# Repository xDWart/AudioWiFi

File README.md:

# AudioWiFi
Самодельный USB-свисток с микрофоном, STM32 и ESP8266 на борту

**AudioWiFi.ioc** - проект STM32CubeMX (v.4.15.0)

**EWARM\Project.eww** - проект IAR Embedded Workbench IDE for ARM (v.7.70.1)

**EagleCAD\** - проект EagleCAD (v.7.7.0)

**ogg.php** - файл серверной части на PHP

**20170303172953.spx** - пример записанного звука

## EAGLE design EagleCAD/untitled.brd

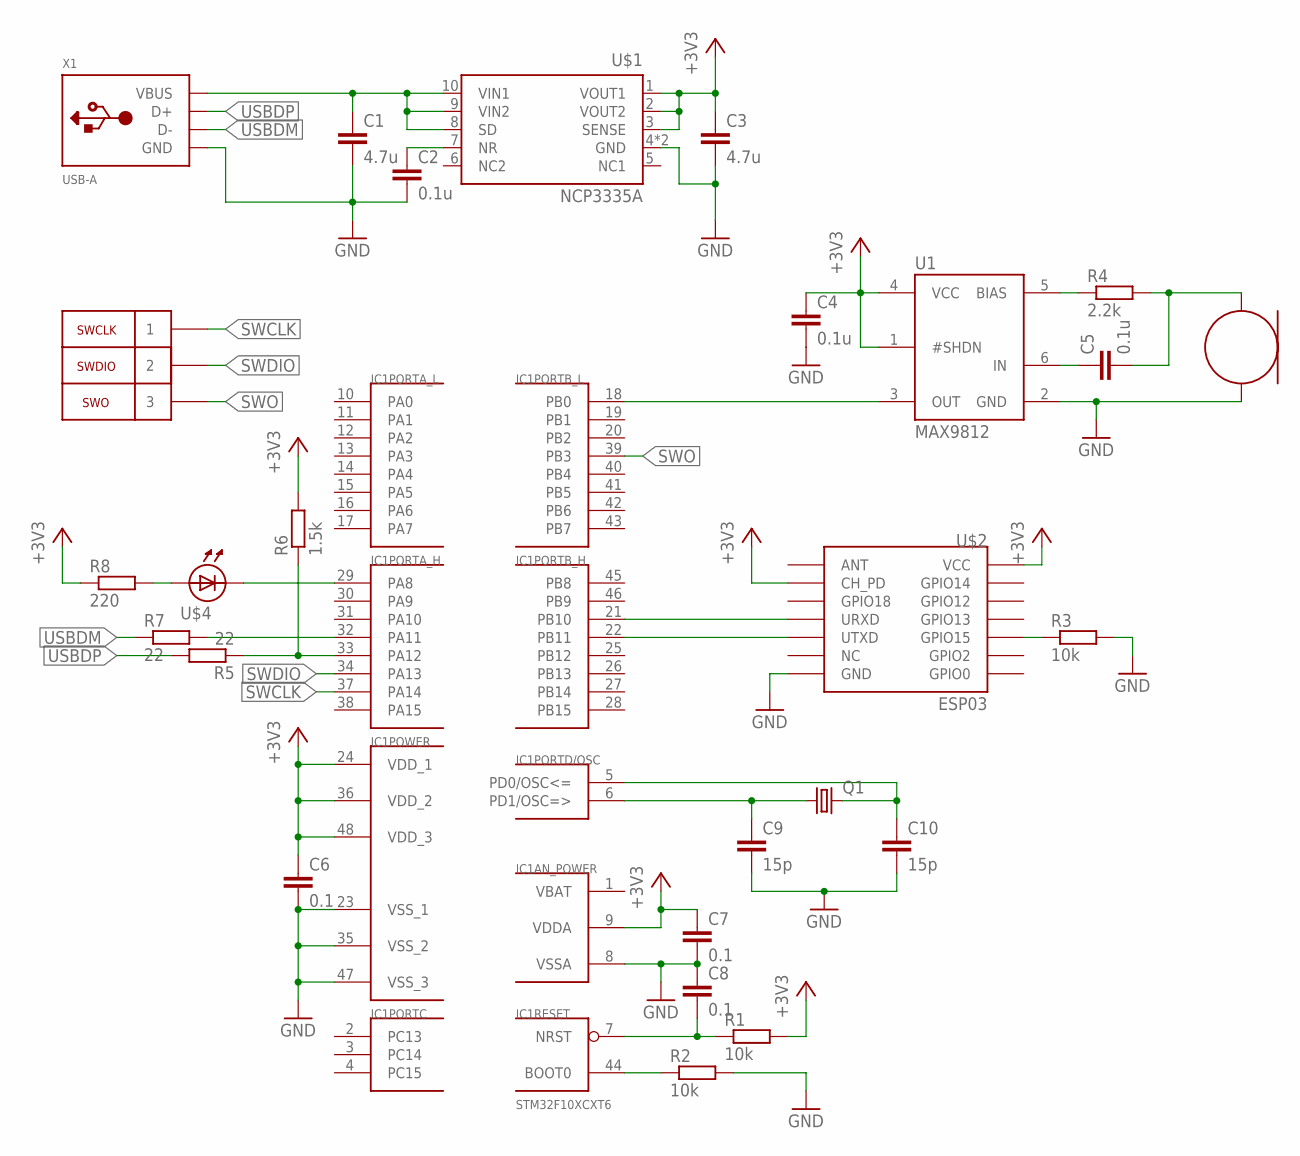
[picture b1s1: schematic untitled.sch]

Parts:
C1, C3: 4.7u; C0805
C2: 0.1u; C0805
C4, C5: 0.1u; C0603
C6, C7, C8: 0.1; C0805
C9, C10: 15p; C0603
IC1: STM32F10XCXT6; TQFP48
Q1: CRYSTAL; DSX321G
R1, R2, R3: 10k; R0805
R4: 2.2k; R0603
R5, R7: 22; R0805
R6: 1.5k; R0805
R8: 220; R0805
U1: MAX9812; SC-70-6
U$1: NCP3335A; DFN10-3X3
U$2: ESP03
U$3: MIC
U$4: LED1206; R1206
U$5: PLS2-3
X1: USB-A; MOLEX_480371000

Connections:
+3V3: C3.1, C4.1, C6.1, C7.1, IC1.9 (VDDA), IC1.24 (VDD_1), IC1.36 (VDD_2), IC1.48 (VDD_3), R1.2, R6.2, R8.1, U1.1 (#SHDN), U1.4 (VCC), U$1.1 (VOUT1), U$1.2 (VOUT2), U$1.3 (SENSE), U$2.CH_PD, U$2.VCC
GND: C1.2, C2.2, C3.2, C4.2, C6.2, C7.2, C8.1, C9.2, C10.2, IC1.8 (VSSA), IC1.23 (VSS_1), IC1.35 (VSS_2), IC1.47 (VSS_3), R2.2, R3.2, U1.2 (GND), U$1.4 (GND), U$1.EXP (GND), U$2.GND, U$3.P$2, X1.4 (GND)
unnamed: C1.1, U$1.8 (SD), U$1.9 (VIN2), U$1.10 (VIN1), X1.1 (VBUS)
unnamed: C2.1, U$1.7 (NR)
unnamed: C8.2, IC1.7 (NRST), R1.1
unnamed: IC1.44 (BOOT0), R2.1
unnamed: IC1.21 (PB10), U$2.URXD
unnamed: IC1.22 (PB11), U$2.UTXD
unnamed: R3.1, U$2.GPIO15
unnamed: IC1.18 (PB0), U1.3 (OUT)
unnamed: R4.1, U1.5 (BIAS)
unnamed: C5.1, U1.6 (IN)
unnamed: C5.2, R4.2, U$3.P$1
unnamed: IC1.33 (PA12), R5.1, R6.1
unnamed: IC1.32 (PA11), R7.2
unnamed: C9.1, IC1.6 (PD1/OSC=>), Q1.P$1 (1)
unnamed: C10.1, IC1.5 (PD0/OSC<=), Q1.P$3 (2)
unnamed: R8.2, U$4.1
unnamed: IC1.29 (PA8), U$4.2
SWCLK: IC1.37 (PA14), U$5.P$1 (1)
SWDIO: IC1.34 (PA13), U$5.P$2 (2)
SWO: IC1.39 (PB3), U$5.P$3 (3)
USBDM: R7.1, X1.2 (D-)
USBDP: R5.2, X1.3 (D+)
VBAT: IC1.1 (VBAT)

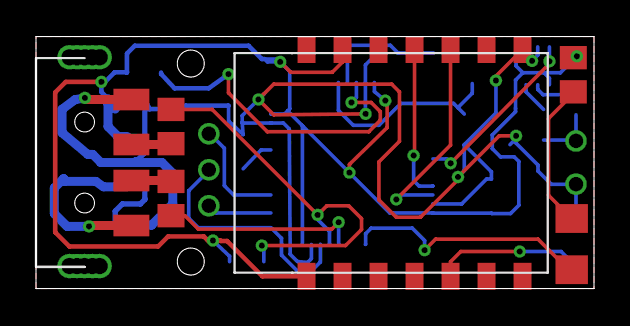
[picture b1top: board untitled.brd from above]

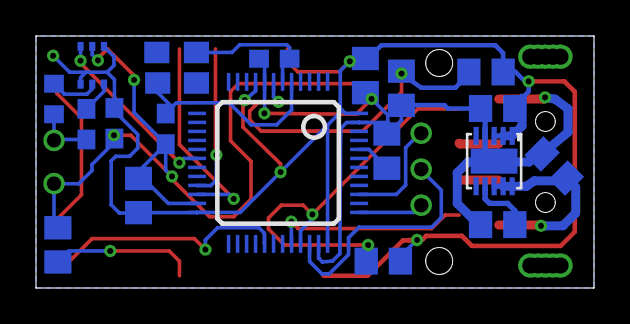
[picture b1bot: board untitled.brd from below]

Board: 2 copper layers, 31.0 x 14.0 mm, 27 parts (19 on the bottom side), 24 nets.

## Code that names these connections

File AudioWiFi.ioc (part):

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Mcu.Name=STM32F103C(8-B)Tx
Mcu.Package=LQFP48
Mcu.UserName=STM32F103CBTx
PA11.Mode=Device
PA11.Signal=USB_DM
PA12.Mode=Device
PA12.Signal=USB_DP
PA13.Mode=Serial_Wire
PA13.Signal=SYS_JTMS-SWDIO
PA14.Mode=Serial_Wire
PA14.Signal=SYS_JTCK-SWCLK
PA8.Signal=GPIO_Output
PB0.Signal=ADCx_IN8
PB10.Mode=Asynchronous
PB10.Signal=USART3_TX
PB11.Mode=Asynchronous
PB11.Signal=USART3_RX
PB3.Signal=SYS_JTDO-TRACESWO
PD0-OSC_IN.Mode=HSE-External-Oscillator
PD0-OSC_IN.Signal=RCC_OSC_IN
PD1-OSC_OUT.Mode=HSE-External-Oscillator
PD1-OSC_OUT.Signal=RCC_OSC_OUT
RCC.SYSCLKFreq_VALUE=72000000
RCC.SYSCLKSource=RCC_SYSCLKSOURCE_PLLCLK
board=AudioWiFi

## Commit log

2017-03-07 Add project
2017-03-08 Update stack/heap size
